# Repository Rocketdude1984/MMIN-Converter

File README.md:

# MM-IN Converter

Simple converter for mm to inches and inches to mm. Meant as a project to advance skills in PCB design and firmware development.

## Power
2xAA batteries

## Parts
- OLED screen - 2.23 Inch OLED LCD Display Module SSD1305 Drive IC 24 Pin 12832 LCD Screen Board 128x32 SPI Interface White https://www.amazon.com/dp/B0DYXSCPYH?ref_=ppx_hzsearch_conn_dt_b_fed_asin_title_5
- Battery Holder - Philmore BH321P https://www.ebay.com/itm/175575917461

## Prototype
- Button Matrix
- 128x32 OLED
- STM32F103C8 MCU
- TPS63020 buck-boost converter (3.3v)
- TPS61040 boost converter (12v)
- 2xAA battery holder

Production took a while longer than expected, but the project is complete.

After correcting a few lines of code the converter works great.

## Construction

1. Make sure to solder the battery holder correctly.
2. Connect the OLED display to the connector before glueing any parts on.
3. I used a resin printer to make the battery shim and display holder and glued them to the board with gorilla glue.

## Changes
I made a few changes to the PCB based on what I learned from this first model.
Mainly I forgot to put the pin designations for the serial connections on the silkscreen. And having an "ON/OFF" indication would have been nice. I tried to implement that in a new version of the board, but it is still not great because screen and battery comepletely cover each side of the switch.

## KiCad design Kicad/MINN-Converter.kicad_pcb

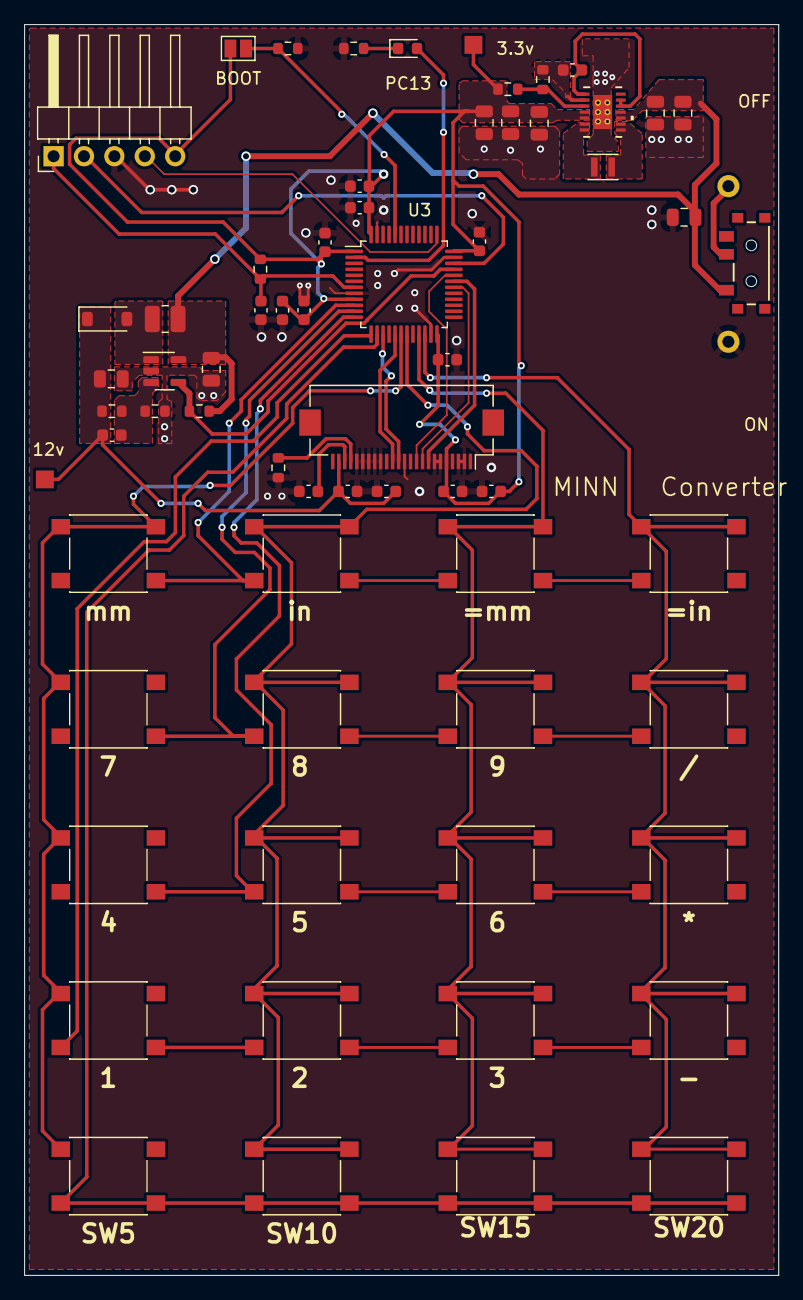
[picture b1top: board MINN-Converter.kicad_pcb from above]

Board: 2 copper layers, 63.0 x 104.5 mm, 65 parts (0 on the bottom side), 33 nets.

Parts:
3.3v: +3.3V; TestPoint_Pad_1.5x1.5mm
12v: +12V; TestPoint_Pad_1.5x1.5mm
BOOT: SolderJumper_2_Open; SolderJumper-2_P1.3mm_Open_Pad1.0x1.5mm
C1: 4µF; C_0805_2012Metric
C2: 4.7µF; C_0805_2012Metric
C3, C4, C12, C15: 100nF; C_0603_1608Metric
C5, C11: 10nF; C_0603_1608Metric
C6, C13, C14: 1µF; C_0603_1608Metric
C7: 4.7µF; C_0603_1608Metric
C8, C9, C10: 100nf; C_0603_1608Metric
C17: 22µF; C_0805_2012Metric
C_COMH1: 1µF; C_0603_1608Metric
C_FF1: 3.3pF; C_0603_1608Metric
C_IN_1, C_IN_2: 10µF; C_0805_2012Metric
C_OUT_1, C_OUT_2, C_OUT_3: 22µF; C_0805_2012Metric
D1: MBR0530; D_SOD-123
D2: LED; LED_0603_1608Metric
J1: SERIAL DEBUG; PinHeader_1x05_P2.54mm_Horizontal
J2: OLED CONN; Hirose_FH12-24S-0.5SH_1x24-1MP_P0.50mm_Horizontal
L1: 3.3µH; L_1008_2520Metric
L2: 1µH, 57mΩ; L_Murata_DFE201610P
R1: 875kΩ; R_0603_1608Metric
R2, R9: 100kΩ; R_0603_1608Metric
R3, R8: 1MΩ; R_0603_1608Metric
R4: 180kΩ; R_0603_1608Metric
R5, R6: 10kΩ; R_0603_1608Metric
R7: 330; R_0603_1608Metric
SW1, SW2, SW3, SW4, SW5, SW6, SW7, SW8, SW9, SW10, SW11, SW12, SW13, SW14, SW15, SW16, SW17, SW18, SW19, SW20: SW_Push; SW_Push_1P1T_NO_6x6mm_H9.5mm
SW21: MK-12C02-G020; MK-12C02-G020_GSW
U1: TPS61040DBV; SOT-23-5
U2: TPS63020QDSJTQ1; DSJ14_2P85X1P58_TEX
U3: STM32F103C8Tx; LQFP-48_7x7mm_P0.5mm

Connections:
+3.3V: 3.3v.1, BOOT.2 (B), C4.1, C5.2, C6.1, C7.1, C8.1, C9.1, C10.1, C12.1, C13.1, C_OUT_1.1, C_OUT_2.1, C_OUT_3.1, J1.5, J2.5, R3.1, R5.1, U2.4 (VOUT), U2.5 (VOUT), U3.1 (VBAT), U3.9 (VDDA), U3.24 (VDD), U3.36 (VDD), U3.48 (VDD)
+12V: 12v.1, C2.1, C14.2, C15.2, C_FF1.1, D1.1 (K), J2.23, R1.1
BOOT0: BOOT.1 (A), R6.1, U3.44 (BOOT0)
COL_1: SW1.2, SW6.2, SW11.2, SW16.2, U3.10 (PA0)
COL_2: SW2.2, SW7.2, SW12.2, SW17.2, U3.11 (PA1)
COL_3: SW3.2, SW8.2, SW13.2, SW18.2, U3.12 (PA2)
COL_4: SW4.2, SW9.2, SW14.2, SW19.2, U3.13 (PA3)
COL_5: SW5.2, SW10.2, SW15.2, SW20.2, U3.14 (PA4)
CS: J2.8, U3.31 (PA10)
D/C: J2.10, U3.32 (PA11)
GND: C1.2, C2.2, C3.2, C4.2, C5.1, C6.2, C7.2, C8.2, C9.2, C10.2, C11.2, C12.2, C13.2, C14.1, C15.1, C17.2, C_COMH1.2, C_IN_1.2, C_IN_2.2, C_OUT_1.2, C_OUT_2.2, C_OUT_3.2, J1.3, J2.2, J2.3, J2.6, J2.7, J2.12, J2.16, J2.17, J2.18, J2.19, J2.20, R2.2, R4.2, R6.2, R7.1, R8.2, U1.2 (GND), U2.2 (GND), U2.15 (EPAD), U2.V, U3.8 (VSSA), U3.23 (VSS), U3.35 (VSS), U3.47 (VSS)
LED: D2.2 (A), U3.2 (PC13)
MOSI: J2.14, U3.17 (PA7)
NRST: C11.1, J1.1, R5.2, U3.7 (NRST)
unnamed: D1.2 (A), L1.2, U1.1 (SW)
unnamed: D2.1 (K), R7.2
unnamed: J2.21, R8.1
unnamed: C_COMH1.1, J2.22
unnamed: L2.1, U2.8 (L1), U2.9 (L1)
unnamed: L2.2, U2.6 (L2), U2.7 (L2)
unnamed: C_FF1.2, R1.2, R2.1, U1.3 (FB)
unnamed: C3.1, U2.1 (VINA), U2.12 (EN), U2.13 (PS/SYNC)
unnamed: R3.2, R4.1, U2.3 (FB)
RES: J2.9, U3.30 (PA9)
ROW_1: SW1.1, SW2.1, SW3.1, SW4.1, SW5.1, U3.18 (PB0)
ROW_2: SW6.1, SW7.1, SW8.1, SW9.1, SW10.1, U3.19 (PB1)
ROW_3: SW11.1, SW12.1, SW13.1, SW14.1, SW15.1, U3.21 (PB10)
ROW_4: SW16.1, SW17.1, SW18.1, SW19.1, SW20.1, U3.22 (PB11)
SCK: J2.13, U3.15 (PA5)
SWCLK: J1.4, U3.37 (PA14)
SWDIO: J1.2, U3.34 (PA13)
SW_OUT: C1.1, C17.1, C_IN_1.1, C_IN_2.1, L1.1, R9.1, SW21.1, U1.5 (VIN), U2.10 (VIN), U2.11 (VIN)
VCC_EN: R9.2, U1.4 (EN), U3.33 (PA12)

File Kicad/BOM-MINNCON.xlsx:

Comment | Designator | Footprint | LCSC Part Number
4.7µF | C1,C2 | Capacitor_SMD:C_0805_2012Metric
100nF | C3, C4, C12, C15 | Capacitor_SMD:C_0603_1608Metric
10nF | C5, C11 | Capacitor_SMD:C_0603_1608Metric
1µF | C6, C13, C14, C_COMH1 | Capacitor_SMD:C_0603_1608Metric
4.7µF | C7 | Capacitor_SMD:C_0603_1608Metric
100nf | C8, C9, C10 | Capacitor_SMD:C_0603_1608Metric
22µF | C17, C_OUT_1, C_OUT_2, C_OUT_3 | Capacitor_SMD:C_0805_2012Metric
3.3pF | C_FF1 | Capacitor_SMD:C_0603_1608Metric
10µF | C_IN_1, C_IN_2 | Capacitor_SMD:C_0805_2012Metric
MBR0530 | D1 | Diode_SMD:D_SOD-123
LED | D2 | LED_SMD:LED_0603_1608Metric
SERIAL DEBUG | J1 | Connector_PinHeader_2.54mm:PinHeader_1x05_P2.54mm_Horizontal
OLED CONN | J2 | Connector_FFC-FPC:Hirose_FH12-24S-0.5SH_1x24-1MP_P0.50mm_Horizontal
3.3µH | L1 | Inductor_SMD:L_1008_2520Metric
1µH, 57mΩ | L2 | Inductor_SMD:L_Murata_DFE201610P
875kΩ | R1 | Resistor_SMD:R_0603_1608Metric
100kΩ | R2, R9 | Resistor_SMD:R_0603_1608Metric
1MΩ | R3, R8 | Resistor_SMD:R_0603_1608Metric
180kΩ | R4 | Resistor_SMD:R_0603_1608Metric
10kΩ | R5, R6 | Resistor_SMD:R_0603_1608Metric
330Ω | R7 | Resistor_SMD:R_0603_1608Metric
SW_Push | SW1, SW2, SW3, SW4, SW5, SW6, SW7, SW8, SW9, SW10, SW11, SW12, SW13, SW14, SW15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 | Button_Switch_SMD:SW_Push_1P1T_NO_6x6mm_H9.5mm
MK-12C02-G020 | SW21 | MK12C02:MK-12C02-G020_GSW
TPS61040DBV | U1 | Package_TO_SOT_SMD:SOT-23-5
TPS63020QDSJTQ1 | U2 | TPS63020:DSJ14_2P85X1P58_TEX
STM32F103C8Tx | U3 | Package_QFP:LQFP-48_7x7mm_P0.5mm

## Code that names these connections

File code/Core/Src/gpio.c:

/* USER CODE BEGIN Header */
/**
  ******************************************************************************
  * @file    gpio.c
  * @brief   This file provides code for the configuration
  *          of all used GPIO pins.
  ******************************************************************************
  * @attention
  *
  * Copyright (c) 2026 STMicroelectronics.
  * All rights reserved.
  *
  * This software is licensed under terms that can be found in the LICENSE file
  * in the root directory of this software component.
  * If no LICENSE file comes with this software, it is provided AS-IS.
  *
  ******************************************************************************
  */
/* USER CODE END Header */

/* Includes ------------------------------------------------------------------*/
#include "gpio.h"

/* USER CODE BEGIN 0 */

/* USER CODE END 0 */

/*----------------------------------------------------------------------------*/
/* Configure GPIO                                                             */
/*----------------------------------------------------------------------------*/
/* USER CODE BEGIN 1 */

/* USER CODE END 1 */

/** Configure pins as
        * Analog
        * Input
        * Output
        * EVENT_OUT
        * EXTI
*/
void MX_GPIO_Init(void)
{

  GPIO_InitTypeDef GPIO_InitStruct = {0};

  /* GPIO Ports Clock Enable */
  __HAL_RCC_GPIOC_CLK_ENABLE();
  __HAL_RCC_GPIOA_CLK_ENABLE();
  __HAL_RCC_GPIOB_CLK_ENABLE();

  /*Configure GPIO pin Output Level */
  HAL_GPIO_WritePin(LED_GPIO_Port, LED_Pin, GPIO_PIN_RESET);

  /*Configure GPIO pin Output Level */
  HAL_GPIO_WritePin(GPIOA, GPIO_PIN_0|GPIO_PIN_1|GPIO_PIN_2|GPIO_PIN_3
                          |GPIO_PIN_4|CS_Pin|D_C_Pin, GPIO_PIN_SET);

  /*Configure GPIO pin Output Level */
  HAL_GPIO_WritePin(GPIOA, RES_Pin|VCC_EN_Pin, GPIO_PIN_RESET);

  /*Configure GPIO pin : LED_Pin */
  GPIO_InitStruct.Pin = LED_Pin;
  GPIO_InitStruct.Mode = GPIO_MODE_OUTPUT_PP;
  GPIO_InitStruct.Pull = GPIO_NOPULL;
  GPIO_InitStruct.Speed = GPIO_SPEED_FREQ_LOW;
  HAL_GPIO_Init(LED_GPIO_Port, &GPIO_InitStruct);

  /*Configure GPIO pins : PA0 PA1 PA2 PA3
                           PA4 RES_Pin CS_Pin D_C_Pin
                           VCC_EN_Pin */
  GPIO_InitStruct.Pin = GPIO_PIN_0|GPIO_PIN_1|GPIO_PIN_2|GPIO_PIN_3
                          |GPIO_PIN_4|RES_Pin|CS_Pin|D_C_Pin
                          |VCC_EN_Pin;
  GPIO_InitStruct.Mode = GPIO_MODE_OUTPUT_PP;
  GPIO_InitStruct.Pull = GPIO_NOPULL;
  GPIO_InitStruct.Speed = GPIO_SPEED_FREQ_LOW;
  HAL_GPIO_Init(GPIOA, &GPIO_InitStruct);

  /*Configure GPIO pins : PB0 PB1 PB10 PB11 */
  GPIO_InitStruct.Pin = GPIO_PIN_0|GPIO_PIN_1|GPIO_PIN_10|GPIO_PIN_11;
  GPIO_InitStruct.Mode = GPIO_MODE_INPUT;
  GPIO_InitStruct.Pull = GPIO_PULLUP;
  HAL_GPIO_Init(GPIOB, &GPIO_InitStruct);

}

/* USER CODE BEGIN 2 */

/* USER CODE END 2 */

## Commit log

2026-02-19 Add project goals to documentation
    Document project goals including needs and wants.
2026-02-19 Update project timeline in goals document
    Added timeline details for project phases.
2026-02-23 Add KeyProcessing.c for key input handling
2026-02-24 Add unit conversion and string formatting functions
    Implement a function to convert various units to a base unit and format the output as a string.
2026-02-24 Mark project as WIP in README
    Update project title to indicate work in progress.
2026-02-24 Correct expression for parsing in main function
    Fix the expression to parse for correct evaluation.
2026-02-24 Rename converToBaseUnit.c to convertToBaseUnit.c
2026-02-25 Refactor conversion and buffer splitting logic
2026-02-25 Implement string to output conversion with parsing
2026-02-26 Final Calculation function
    Refactor stringToOutput.c to use char pointers and add unit conversion functionality.
2026-02-26 Rename stringToOutput.c to calculation.c
2026-02-26 Refactor key processing to use append functions
2026-02-26 Refactor key processing to use calculator_t structure
    Refactor key processing functions to use a calculator_t structure for state management. Update function signatures and implementations to accommodate the new structure.
2026-02-26 Parser, key processing, and converter
    This is the program that first builds a string with key presses, then converts the string to the base unit (mm) reformatting the string to then be calculated in the math parser, calculation(), and th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
2026-02-26 Refactor conversion and calculation functions
    Updated conversion functions to handle units and error cases. Increased output buffer size and modified calculations for better accuracy.
2026-02-26 Add parseFloat function for string to float conversion
    Implement parseFloat function to convert string to float.
2026-02-26 Add button press handling in buttonPress.c
2026-02-26 Clean up buttonPress.c by removing unused code
    Removed unused variables and commented out UART transmission.
2026-02-28 Core Folder for stm32IDE
2026-02-28 Block Diagram for current Logic FLow
2026-03-01 Updated Core Folder
2026-03-11 Add placeholder.md with initial content
2026-03-11 Files for the font libraries and main.c
    This is just here for now, will later be made into it's own header and source file for the main program.
2026-03-15 Implement splitBuffer and convert functions
    Added a function to split and convert input strings with units.
2026-03-15 Updating Code
    Added display control, fonts, and fixed bugs
2026-03-15 Remove unnecessary comments and clean up main.c
    Got tired, this needs more work later.
2026-03-18 Reuploading core files
    Fixed some bugs and removed the external crystal source and now using the internal clock.
2026-03-20 Adding prototype description
2026-03-21 Prototype Image
2026-03-21 Include project timeline image in README
    Added project timeline image to README.
2026-03-21 Update image format for project prototype
2026-05-09 Uploading Finally core files
    Fixed OLED initialization, and changed to use internal clock.
2026-05-09 3D printed parts folder
2026-05-09 Add placeholder markdown file
2026-05-09 Uploads for the kicad project files
    Kicad project files, gerber files for manufacturing, BOM, and position file.
2026-05-09 Revise README with project details and updates
    Updated project title and added construction details and changes made to the PCB based on the first model's learnings.
2026-05-09 Uploading images
2026-05-09 Update README with power and parts information
    Added power requirements and parts list to README.
2026-05-09 Fix formatting for parts section in README
2026-05-09 Rename project in README
    Updated project name from 'MMIN-Converter' to 'MM-IN Converter'.
